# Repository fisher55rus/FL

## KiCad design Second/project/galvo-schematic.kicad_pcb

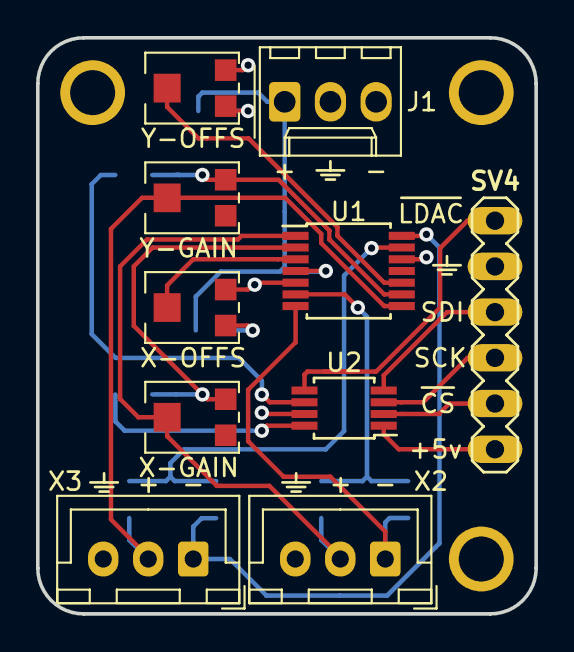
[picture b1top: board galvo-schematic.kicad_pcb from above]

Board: 2 copper layers, 27.7 x 32.0 mm, 18 parts (0 on the bottom side), 21 nets.

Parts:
J1: 0022272031; Molex_KK-254_AE-6410-03A_1x03_P2.54mm_Vertical
R1, R5: 1k; R_0805_2012Metric_Pad1.15x1.40mm_HandSolder
R2, R6: 47k; R_0603_1608Metric_Pad1.05x0.95mm_HandSolder
R3, R7, R11, R12: 10k; R_0805_2012Metric_Pad1.15x1.40mm_HandSolder
SV4: MA06-1
U1: TL084; TSSOP-14_4.4x5mm_P0.65mm
U2: MCP4822; MSOP-8_3x3mm_P0.65mm
X2, X3: JST-XH-03-PIN-ROUND-PAD; JST_XH_B03B-XH-A_1x03_P2.50mm_Vertical
X-GAIN: 10k; Potentiometer_Murata_PVS3_Vertical
X-OFFS: 10k; Potentiometer_Murata_PVS3_Vertical
Y-GAIN: 10k; Potentiometer_Murata_PVS3_Vertical
Y-OFFS: 10k; Potentiometer_Murata_PVS3_Vertical

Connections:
+5V: SV4.6, U2.1
/+V15: J1.1, R2.1, R6.1, U1.4
/CS: SV4.5, U2.2
/ILDAX+15V: R7.1, U1.1, X2.2, X-GAIN.S
/ILDAX-15V: R11.2, U1.7, X2.1
/ILDAY+15V: R3.1, U1.8, X3.2, Y-GAIN.S
/ILDAY-15V: R12.2, U1.14, X3.1
/LATCH: SV4.1, U2.5
/SCK: SV4.4, U2.3
/SDI: SV4.3, U2.4
GND: J1.2, SV4.2, U1.5, U1.12, U2.7, X2.3, X3.3, X-OFFS.E, Y-OFFS.E
unnamed: R1.1, U2.6
unnamed: R5.1, U2.8
unnamed: R1.2, U1.9, Y-GAIN.E
unnamed: R2.2, Y-OFFS.A
unnamed: R5.2, U1.2, X-GAIN.E
unnamed: R6.2, X-OFFS.A
unnamed: R7.2, R11.1, U1.6
unnamed: R3.2, R12.1, U1.13
unnamed: U1.3, X-OFFS.S
unnamed: U1.10, Y-OFFS.S

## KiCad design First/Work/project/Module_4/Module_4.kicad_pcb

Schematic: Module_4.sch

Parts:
A1: ReoRand_LM2596
A2: Arduino_Nano_v3.x; Arduino_Nano
A3: ZS-042_RTC1; ZS-042
J1: Conn_01x20; klemmnik_x20
J2, J5: Conn_01x08_Female; plc_x8
J3: Conn_01x10_Female; plc_x10
J4: Conn_01x06_Female; plc_x6
SW1: SW_Push

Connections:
/5v: A2.27, A3.5 (VCC), J1.3, J1.13, J5.4
/In+: A1.1 (In+), SW1.2
/In-: A1.2 (In-), J1.2
/a0: A2.19, J1.15
/a1: A2.20, J1.16
/a2: A2.21, J1.17
/a3: A2.22, J1.18
/a4: A2.23, A3.4 (SDA), J1.6
/a5: A2.24, A3.3 (SCL), J1.5
/a6: A2.25, J1.19
/a7: A2.26, J1.20
/d2: A2.5, J1.7
/d3: A2.6, J1.8
/d4: A2.7, J1.9
/d5: A2.8, J1.10
/d6: A2.9, J1.11
/d7: A2.10, J2.8
/d8: A2.11, J3.1
/d9: A2.12, J3.2
/d10: A2.13, J1.12
/gnd: A1.4 (Out-), A2.4, A2.29, A3.6 (GND), J1.4, J1.14, J5.3
/vin: A1.3 (Out+), A2.30
unnamed: J1.1, SW1.1

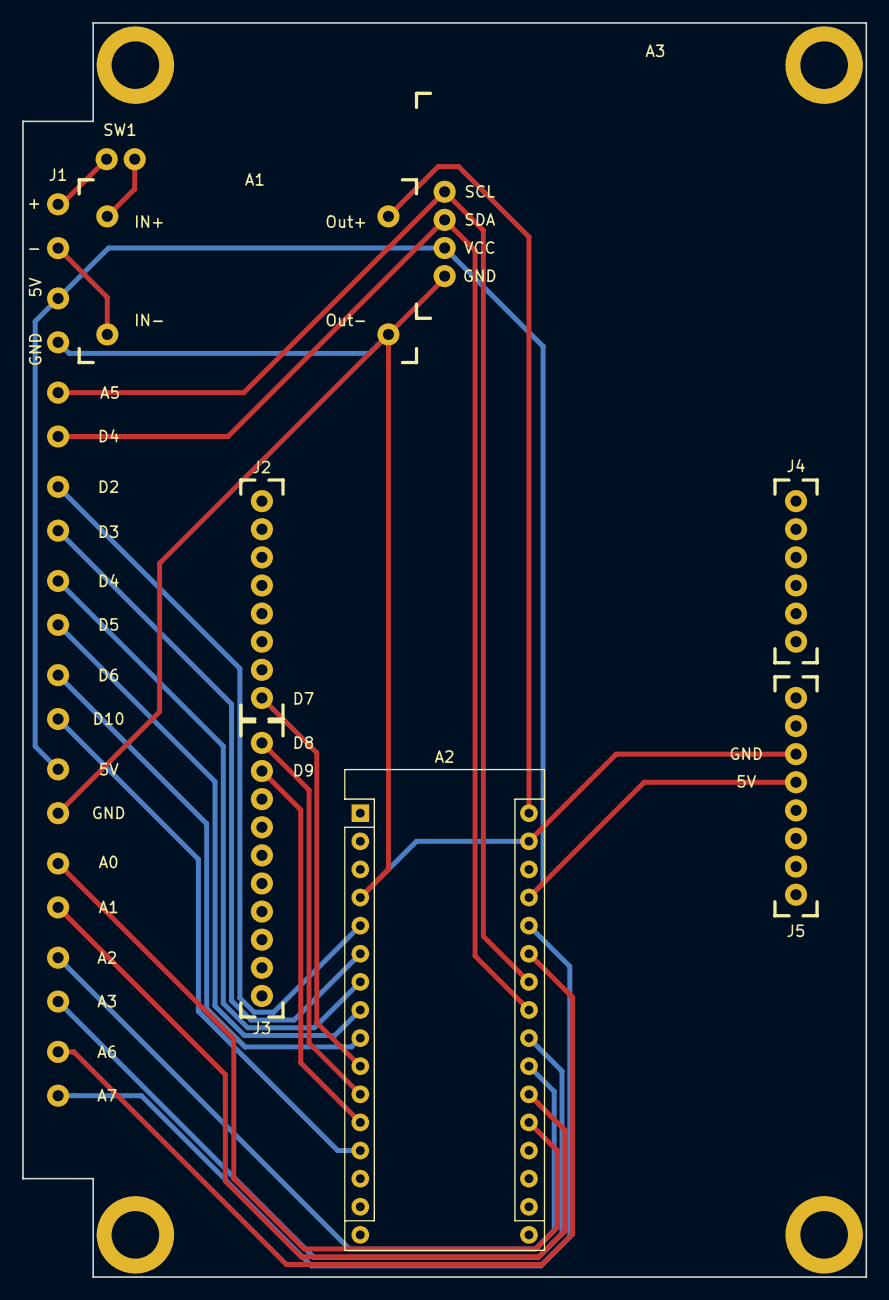
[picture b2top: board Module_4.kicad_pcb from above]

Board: 2 copper layers, 76.2 x 113.3 mm, 9 parts (0 on the bottom side), 23 nets.

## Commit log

2019-02-20 Разработка проекта
2019-02-20 Добавлены 3d-модели, проработан проект
2019-02-21 Поправлена шелкография проекта
2019-02-25 Проект окочен
2019-03-22 Добавлены наработки по второму контракту
2019-03-22 Переработка проекта 2
2019-03-22 Предварительно закончен второй проект
2019-03-23 Очередная корректировка проекта
    Удалена шелкография номиналов резисторов.
    Заменен потенциометр.
2019-03-23 Наведен порядок
2019-03-23 Закончен 2 проект
